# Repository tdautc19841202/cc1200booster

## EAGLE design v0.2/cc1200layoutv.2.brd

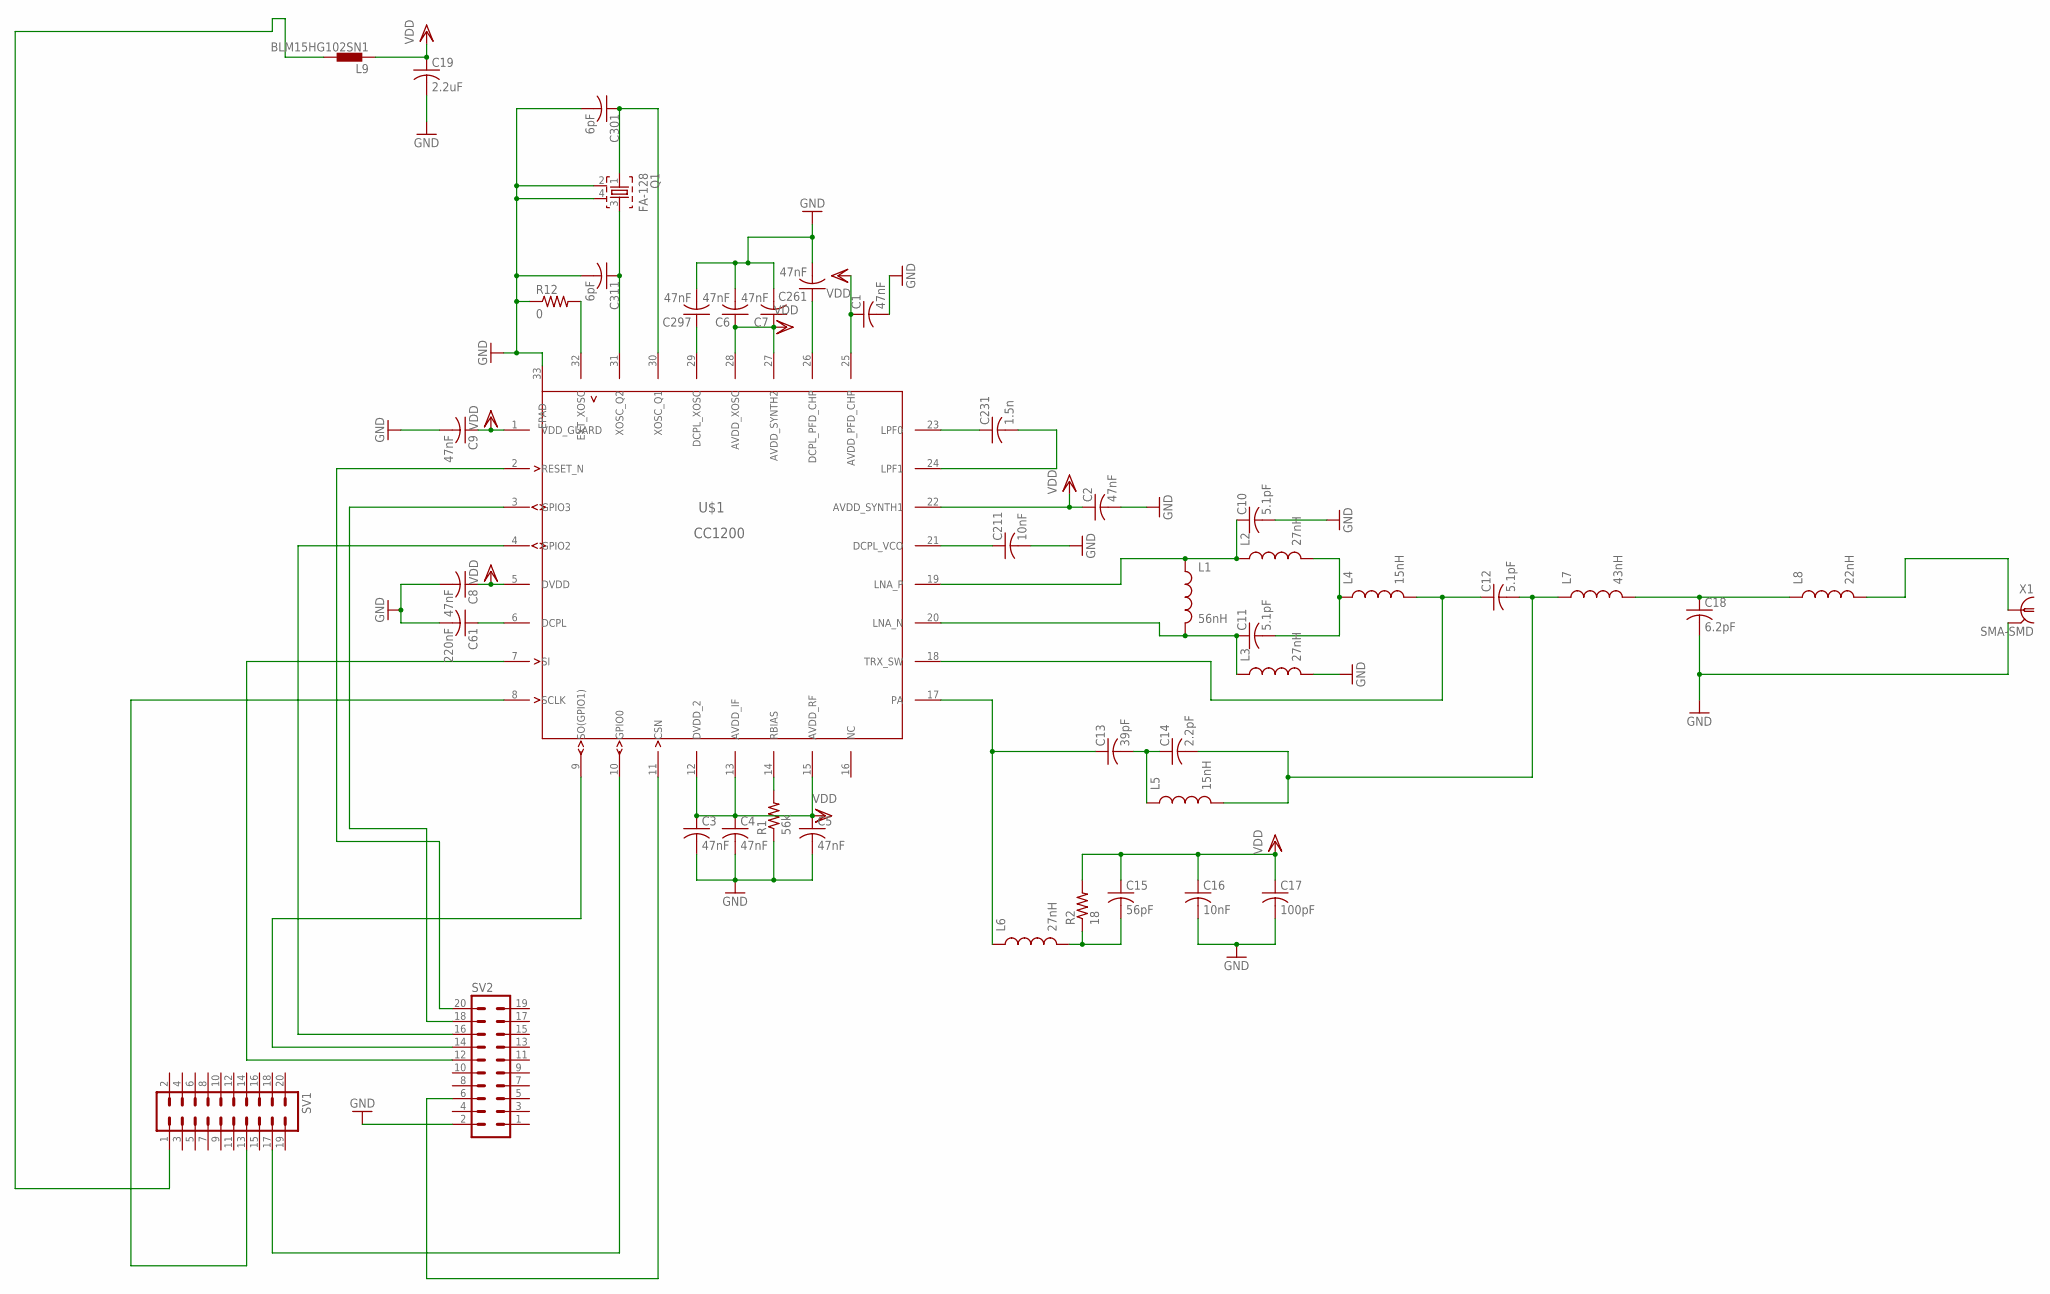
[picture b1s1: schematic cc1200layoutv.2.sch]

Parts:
C1, C2, C3, C4, C5, C6, C7, C8, C9, C261, C297: 47nF; C0402K
C10, C11, C12: 5.1pF; C0402K
C13: 39pF; C0402K
C14: 2.2pF; C0402K
C15: 56pF; C0402K
C16, C211: 10nF; C0402K
C17: 100pF; C0402K
C18: 6.2pF; C0402K
C19: 2.2uF; C0603K
C61: 220nF; C0402K
C231: 1.5n; C0402K
C301, C311: 6pF; C0402K
L1: 56nH; C0402
L2, L3, L6: 27nH; C0402
L4, L5: 15nH; C0402
L7: 43nH; C0402
L8: 22nH; C0402
L9: BLM15HG102SN1; 0402
Q1: FA-128
R1: 56k; R0402
R2: 18; R0402
R12: 0; R0402
SV1, SV2: MA10-2
U$1: CC1200; RHB32_3P45X3P45
X1: SMA-SMD

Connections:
GND: C1.2, C2.2, C3.2, C4.2, C5.2, C6.2, C7.2, C8.2, C9.2, C10.2, C16.2, C17.2, C18.2, C19.2, C61.2, C211.2, C261.2, C297.2, C301.2, C311.2, L3.2, Q1.2, Q1.4, R1.1, R12.1, SV2.2, U$1.33 (EPAD), X1.2@1 (2), X1.2@2 (2), X1.2@3 (2), X1.2@4 (2), X1.2@5 (2), X1.2@6 (2)
unnamed: SV2.12, U$1.7 (SI)
unnamed: SV1.13, U$1.8 (SCLK)
unnamed: SV2.14, U$1.9 (SO(GPIO1))
unnamed: SV1.17, U$1.10 (GPIO0)
unnamed: SV2.6, U$1.11 (CSN)
unnamed: C231.1, U$1.23 (LPF0)
unnamed: C231.2, U$1.24 (LPF1)
unnamed: C211.1, U$1.21 (DCPL_VCO)
unnamed: C261.1, U$1.26 (DCPL_PFD_CHP)
unnamed: C297.1, U$1.29 (DCPL_XOSC)
unnamed: C61.1, U$1.6 (DCPL)
unnamed: R1.2, U$1.14 (RBIAS)
unnamed: R12.2, U$1.32 (EXT_XOSC)
unnamed: C311.1, Q1.3, U$1.31 (XOSC_Q2)
unnamed: SV2.16, U$1.4 (GPIO2)
unnamed: SV2.18, U$1.3 (GPIO3)
unnamed: SV2.20, U$1.2 (RESET_N)
unnamed: C301.1, Q1.1, U$1.30 (XOSC_Q1)
unnamed: C10.1, L1.1, L2.1, U$1.19 (LNA_P)
unnamed: C11.1, L1.2, L3.1, U$1.20 (LNA_N)
unnamed: L9.2, SV1.1
unnamed: C13.1, L6.1, U$1.17 (PA)
unnamed: C11.2, L2.2, L4.1
unnamed: C12.1, L4.2, U$1.18 (TRX_SW)
unnamed: C13.2, C14.1, L5.1
unnamed: C12.2, C14.2, L5.2, L7.1
unnamed: C15.2, L6.2, R2.1
unnamed: C18.1, L7.2, L8.1
unnamed: L8.2, X1.1
VDD: C1.1, C2.1, C3.1, C4.1, C5.1, C6.1, C7.1, C8.1, C9.1, C15.1, C16.1, C17.1, C19.1, L9.1, R2.2, U$1.1 (VDD_GUARD), U$1.5 (DVDD), U$1.12 (DVDD_2), U$1.13 (AVDD_IF), U$1.15 (AVDD_RF), U$1.22 (AVDD_SYNTH1), U$1.25 (AVDD_PFD_CHP), U$1.27 (AVDD_SYNTH2), U$1.28 (AVDD_XOSC)

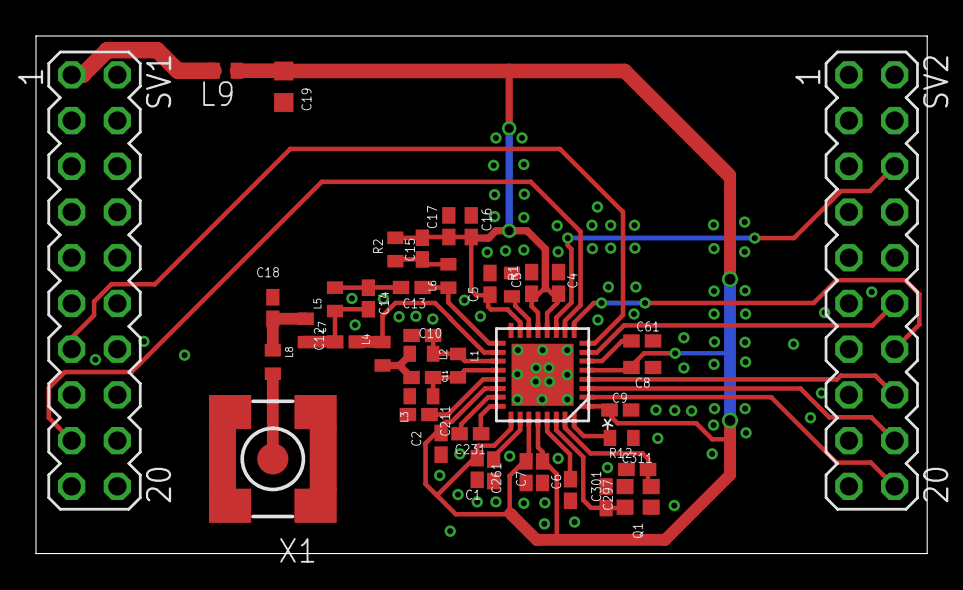
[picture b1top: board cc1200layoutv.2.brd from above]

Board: 2 copper layers, 49.5 x 28.8 mm, 43 parts (0 on the bottom side), 31 nets.

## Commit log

2014-02-19 Layout based on reference design
    boosterpack style
2014-02-19 Boosterpack CC1200
2014-02-20 added image
2014-02-24 Added v0.2
    Made sma surface mount and turned the cc1200 90 degrees clockwise

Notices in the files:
parts and their libraries:
SparkFun-Passives: Licensing: CC v3.0 Share-Alike You are welcome to use this library for commercial purposes.
